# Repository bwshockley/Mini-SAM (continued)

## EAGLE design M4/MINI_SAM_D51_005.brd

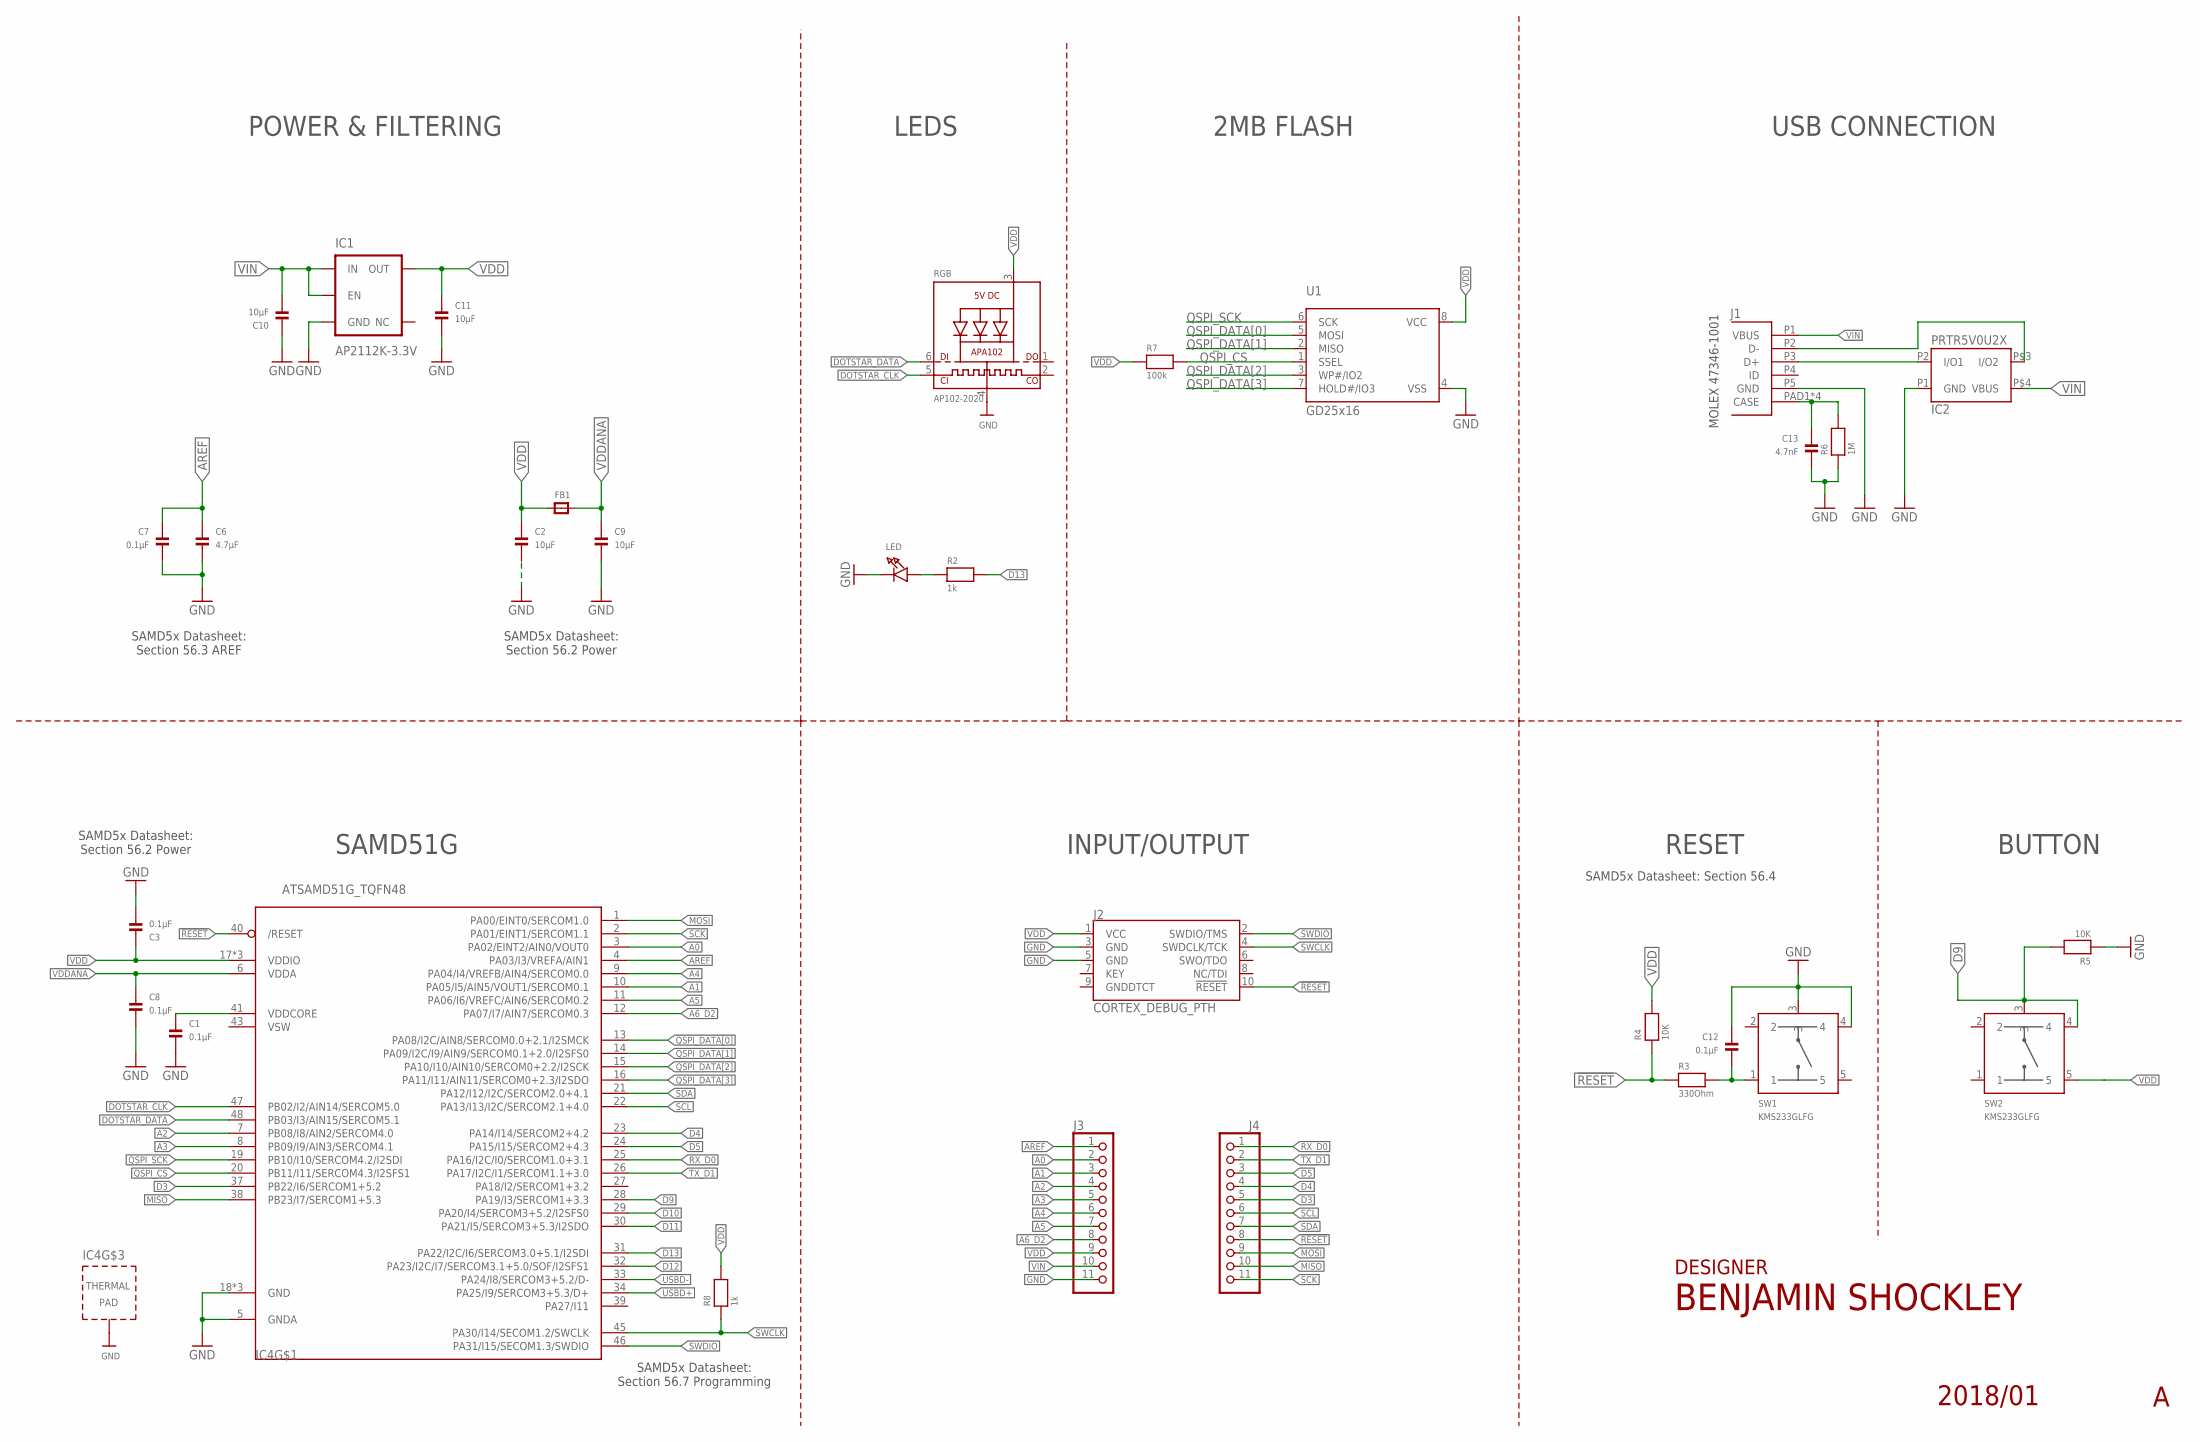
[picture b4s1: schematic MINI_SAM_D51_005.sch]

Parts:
C1, C3, C7, C8, C12: 0.1µF; _0603MP
C2, C9, C10, C11: 10µF; _0603MP
C6: 4.7µF; _0603MP
C13: 4.7nF; _0603MP
FB1: FERRITE_0603MP; _0603MP
IC1: AP2112K-3.3V; SOT23-5
IC2: PRTR5V0U2X; SOT143B_REFLOW
IC4: ATSAMD51G_TQFN48; TQFN48_7MM
J1: MOLEX_47346-100147346; MOLEX_47346-1001
J2: CORTEX_DEBUG_PTH; 2X5-PTH-1.27MM
J3, J4: PINHD-1X111X11_SMT; 1X11_SMT
LED: LED0603_NOOUTLINE; CHIPLED_0603_NOOUTLINE
R2, R8: 1k; _0603MP
R3: 330Ohm; _0603MP
R4, R5: 10K; _0603MP
R6: 1M; _0603MP
R7: 100k; _0603MP
RGB: AP102-2020; APA102_2020
SW1, SW2: KMS233GLFG; KMS_SWITCH
U1: GD25x16; USON8

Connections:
!RESET: IC4.40 (/RESET), J2.10 (!RESET), J4.8, R3.1, R4.1
A0: IC4.3 (PA02/EINT2/AIN0/VOUT0), J3.2
A1: IC4.10 (PA05/I5/AIN5/VOUT1/SERCOM0.1), J3.3
A2: IC4.7 (PB08/I8/AIN2/SERCOM4.0), J3.4
A3: IC4.8 (PB09/I9/AIN3/SERCOM4.1), J3.5
A4: IC4.9 (PA04/I4/VREFB/AIN4/SERCOM0.0), J3.6
A5: IC4.11 (PA06/I6/VREFC/AIN6/SERCOM0.2), J3.7
A6_D2: IC4.12 (PA07/I7/AIN7/SERCOM0.3), J3.8
AREF: C6.1, C7.1, IC4.4 (PA03/I3/VREFA/AIN1), J3.1
D3: IC4.37 (PB22/I6/SERCOM1+5.2), J4.5
D4: IC4.23 (PA14/I14/SERCOM2+4.2), J4.4
D5: IC4.24 (PA15/I15/SERCOM2+4.3), J4.3
D9: IC4.28 (PA19/I3/SERCOM1+3.3), R5.2, SW2.3, SW2.4
D10: IC4.29 (PA20/I4/SERCOM3+5.2/I2SFS0)
D11: IC4.30 (PA21/I5/SERCOM3+5.3/I2SDO)
D12: IC4.32 (PA23/I2C/I7/SERCOM3.1+5.0/SOF/I2SFS1)
D13: IC4.31 (PA22/I2C/I6/SERCOM3.0+5.1/I2SDI), R2.2
DOTSTAR_CLK: IC4.47 (PB02/I2/AIN14/SERCOM5.0), RGB.5 (CKI)
DOTSTAR_DATA: IC4.48 (PB03/I3/AIN15/SERCOM5.1), RGB.6 (DI)
GND: C1.2, C2.2, C3.2, C6.2, C7.2, C8.2, C9.2, C10.1, C11.2, C12.1, C13.2, IC1.2 (GND), IC2.P1 (GND), IC4.5 (GNDA), IC4.18 (GND), IC4.35 (GND), IC4.42 (GND), IC4.THERMAL (TP), J1.P5 (GND), J2.3 (GND), J2.5 (GND), J3.11, LED.C, R5.1, R6.1, RGB.4 (GND), SW1.3, SW1.4, U1.4 (VSS)
MISO: IC4.38 (PB23/I7/SERCOM1+5.3), J4.10
MOSI: IC4.1 (PA00/EINT0/SERCOM1.0), J4.9
unnamed: C13.1, J1.PAD1 (CASE), J1.PAD2 (CASE), J1.PAD3 (CASE), J1.PAD4 (CASE), R6.2
unnamed: LED.A, R2.1
unnamed: C12.2, R3.2, SW1.1
unnamed: C1.1, IC4.41 (VDDCORE)
QSPI_CS: IC4.20 (PB11/I11/SERCOM4.3/I2SFS1), R7.2, U1.1 (SSEL)
QSPI_DATA[0]: IC4.13 (PA08/I2C/AIN8/SERCOM0.0+2.1/I2SMCK), U1.5 (MOSI)
QSPI_DATA[1]: IC4.14 (PA09/I2C/I9/AIN9/SERCOM0.1+2.0/I2SFS0), U1.2 (MISO)
QSPI_DATA[2]: IC4.15 (PA10/I10/AIN10/SERCOM0+2.2/I2SCK), U1.3 (WP#/IO2)
QSPI_DATA[3]: IC4.16 (PA11/I11/AIN11/SERCOM0+2.3/I2SDO), U1.7 (HOLD#/IO3)
QSPI_SCK: IC4.19 (PB10/I10/SERCOM4.2/I2SDI), U1.6 (SCK)
RX_D0: IC4.25 (PA16/I2C/I0/SERCOM1.0+3.1), J4.1
SCK: IC4.2 (PA01/EINT1/SERCOM1.1), J4.11
SCL: IC4.22 (PA13/I13/I2C/SERCOM2.1+4.0), J4.6
SDA: IC4.21 (PA12/I12/I2C/SERCOM2.0+4.1), J4.7
SWCLK: IC4.45 (PA30/I14/SECOM1.2/SWCLK), J2.4 (SWDCLK/TCK), R8.1
SWDIO: IC4.46 (PA31/I15/SECOM1.3/SWDIO), J2.2 (SWDIO/TMS)
TX_D1: IC4.26 (PA17/I2C/I1/SERCOM1.1+3.0), J4.2
USBD+: IC2.P2 (I/O1), IC4.34 (PA25/I9/SERCOM3+5.3/D+), J1.P3 (D+)
USBD-: IC2.P$3 (I/O2), IC4.33 (PA24/I8/SERCOM3+5.2/D-), J1.P2 (D-)
VDD: C2.1, C3.1, C11.1, FB1.1, IC1.5 (OUT), IC4.17 (VDDIO), IC4.36 (VDDIO), IC4.44 (VDDIO), J2.1 (VCC), J3.9, R4.2, R7.1, R8.2, RGB.3 (VDD), SW2.5, U1.8 (VCC)
VDDANA: C8.1, C9.1, FB1.2, IC4.6 (VDDA)
VIN: C10.2, IC1.1 (IN), IC1.3 (EN), IC2.P$4 (VBUS), J1.P1 (VBUS), J3.10
VSW: IC4.43 (VSW)

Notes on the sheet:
INPUT/OUTPUT
RESET
POWER & FILTERING
SAMD51G
LEDS
USB CONNECTION
MOLEX 47346-1001
BUTTON
DESIGNER
SAMD5x Datasheet: Section 56.4
2MB FLASH
SAMD5x Datasheet: Section 56.3 AREF
SAMD5x Datasheet: Section 56.2 Power
SAMD5x Datasheet: Section 56.7 Programming

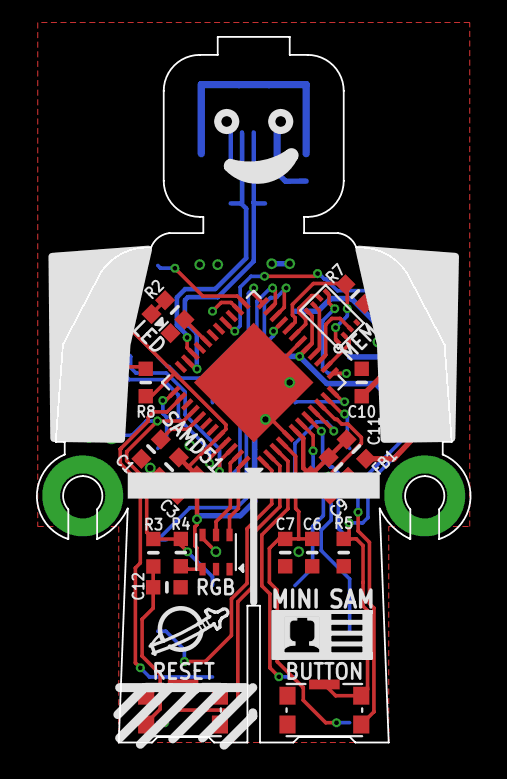
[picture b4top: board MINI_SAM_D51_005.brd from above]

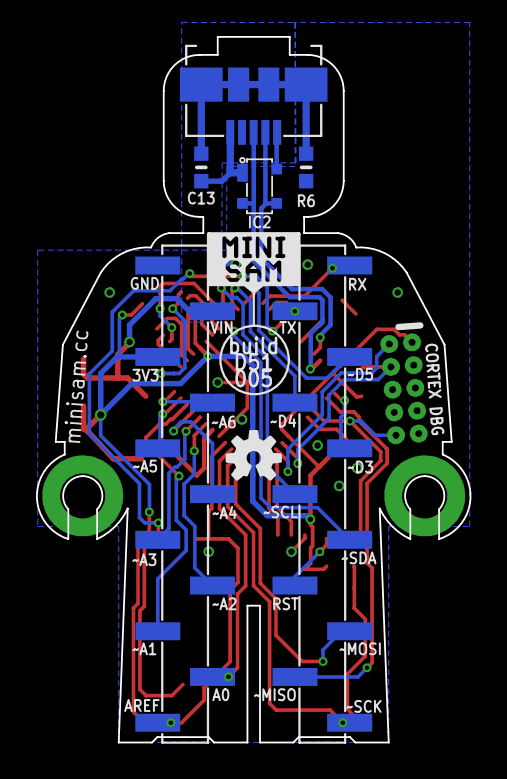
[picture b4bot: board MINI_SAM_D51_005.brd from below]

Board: 2 copper layers, 24.1 x 39.2 mm, 32 parts (7 on the bottom side), 41 nets.

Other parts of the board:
U$3: OSHW-LOGO-S

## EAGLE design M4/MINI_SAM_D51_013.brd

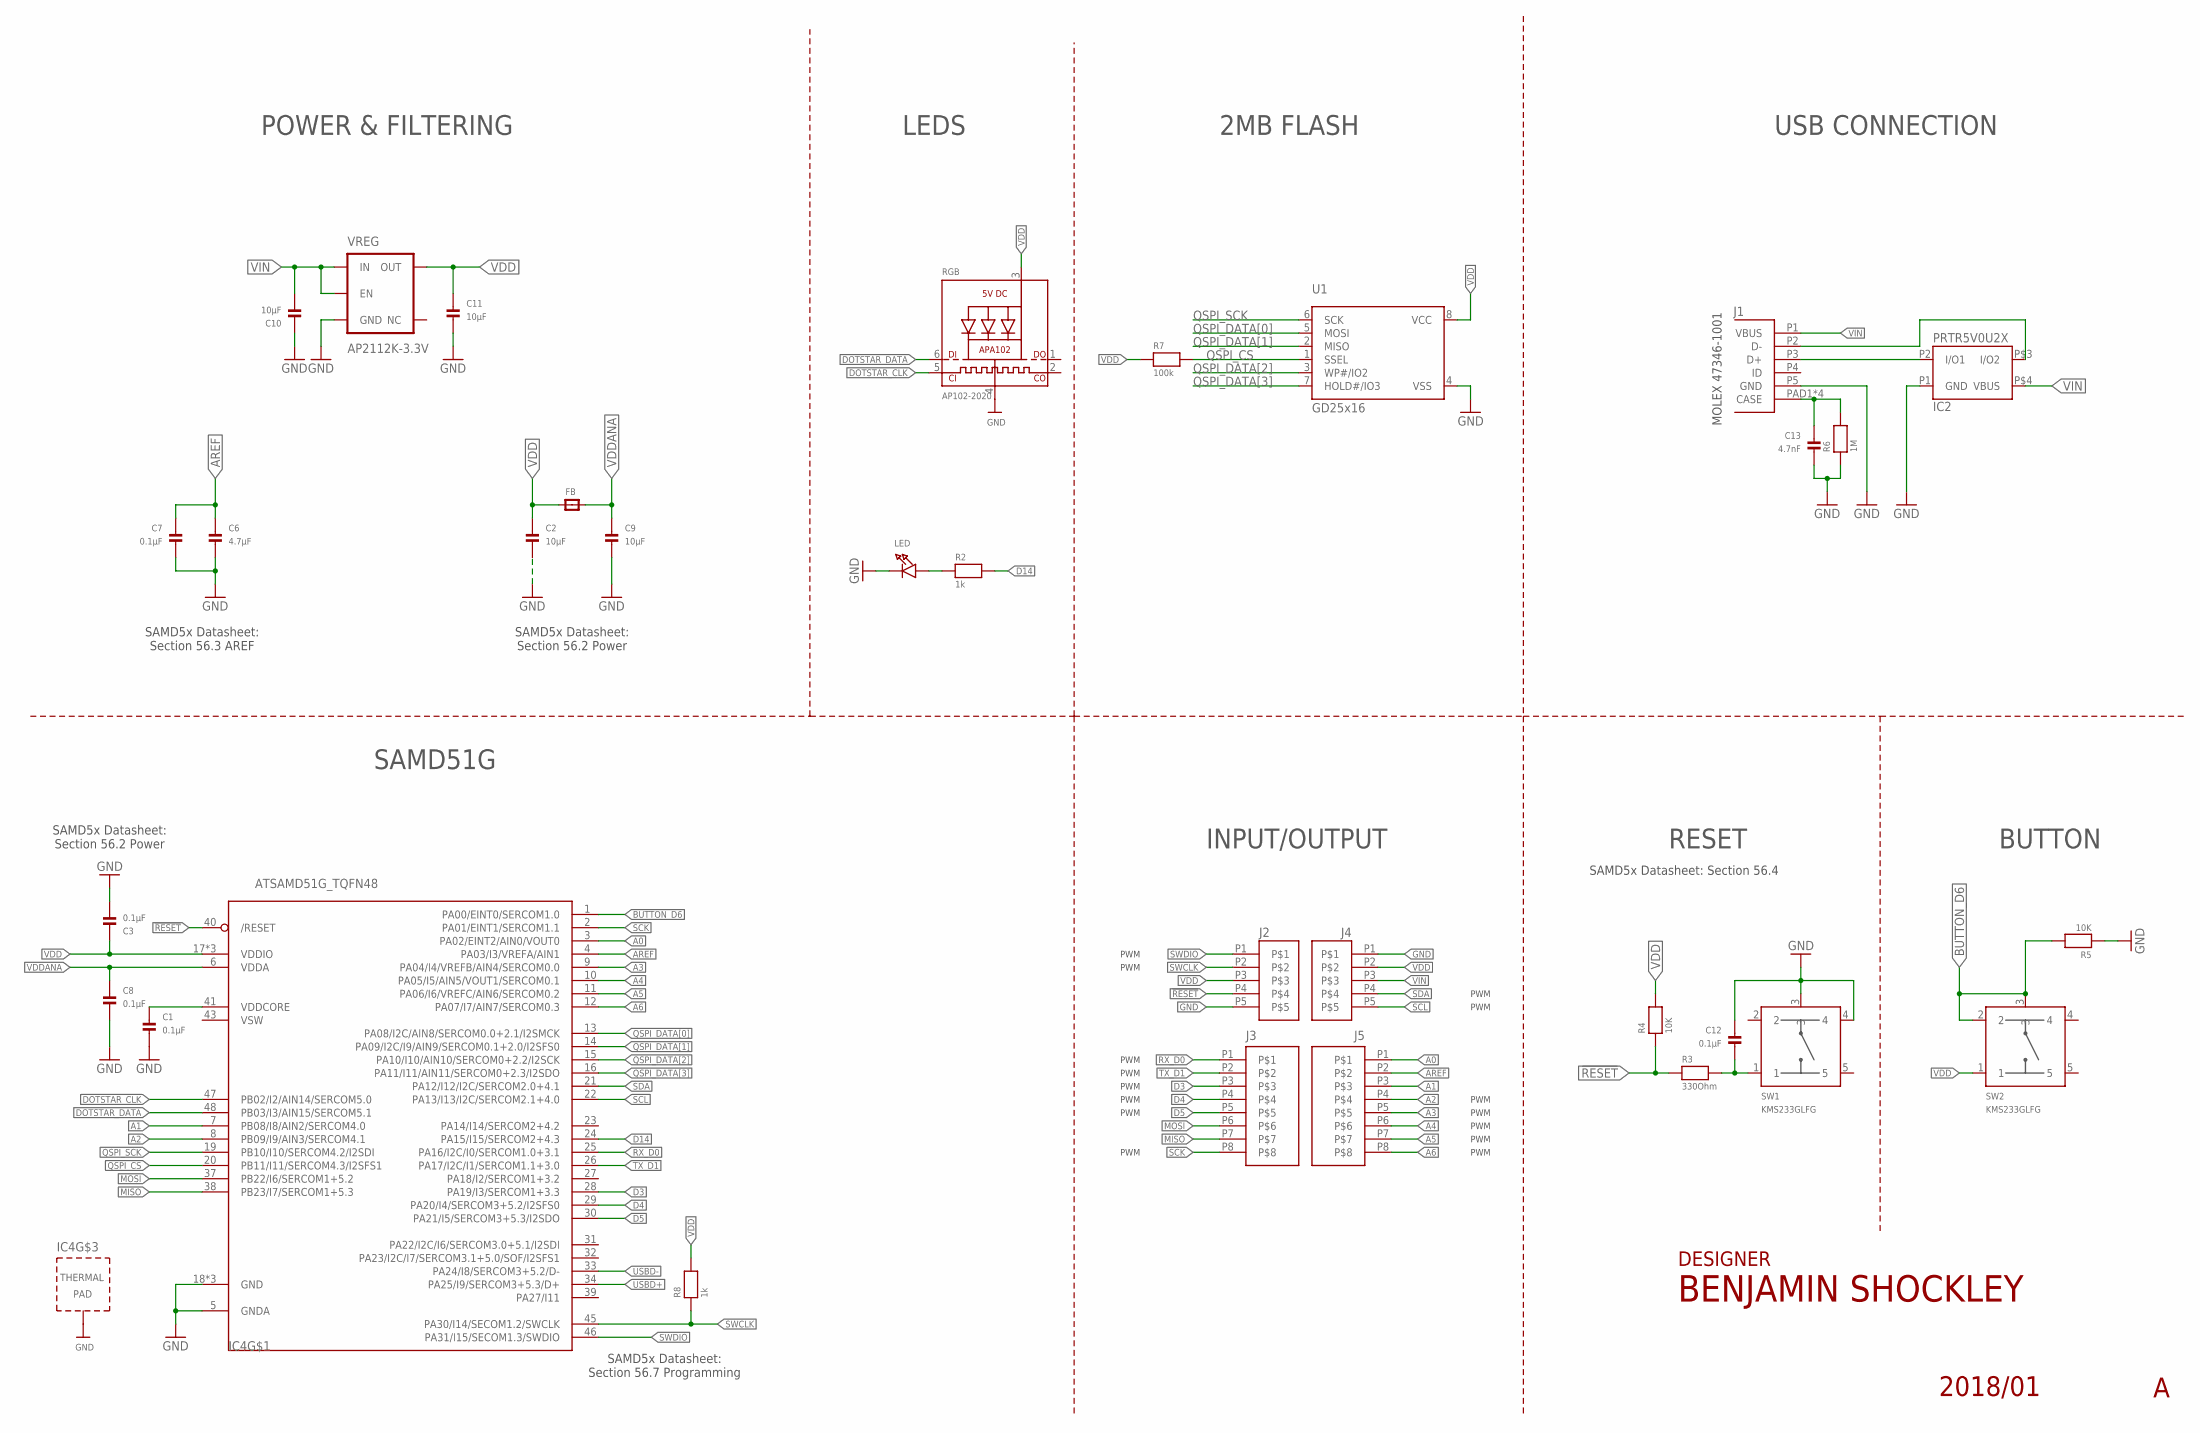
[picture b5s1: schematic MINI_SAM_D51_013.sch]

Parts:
C1, C3, C7, C8, C12: 0.1µF; _0603MP
C2, C9, C10, C11: 10µF; _0603MP
C6: 4.7µF; _0603MP
C13: 4.7nF; _0603MP
FB: FERRITE_0603MP; _0603MP
IC2: PRTR5V0U2X; SOT143B_REFLOW
IC4: ATSAMD51G_TQFN48; TQFN48_7MM
J1: MOLEX_47346-100147346; MOLEX_47346-1001
J2, J4: 1X5_HEADER_1.27MMCAST; 1X5_HEADER_1.27MM_CASTELLATED
J3, J5: 1X8_HEADER_1.27MMCAST; 1X8_HEADER_1.27MM_CASTELLATED
LED: LED0805_NOOUTLINE; CHIPLED_0805_NOOUTLINE
R2, R8: 1k; _0603MP
R3: 330Ohm; _0603MP
R4, R5: 10K; _0603MP
R6: 1M; _0603MP
R7: 100k; _0603MP
RGB: AP102-2020; APA102_2020
SW1, SW2: KMS233GLFG; KMS_SWITCH
U1: GD25x16; USON8
VREG: AP2112K-3.3V; SOT23-5

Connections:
!RESET: IC4.40 (/RESET), J2.P4, R3.1, R4.1
A0: IC4.3 (PA02/EINT2/AIN0/VOUT0), J5.P1
A1: IC4.7 (PB08/I8/AIN2/SERCOM4.0), J5.P3
A2: IC4.8 (PB09/I9/AIN3/SERCOM4.1), J5.P4
A3: IC4.9 (PA04/I4/VREFB/AIN4/SERCOM0.0), J5.P5
A4: IC4.10 (PA05/I5/AIN5/VOUT1/SERCOM0.1), J5.P6
A5: IC4.11 (PA06/I6/VREFC/AIN6/SERCOM0.2), J5.P7
A6: IC4.12 (PA07/I7/AIN7/SERCOM0.3), J5.P8
AREF: C6.1, C7.1, IC4.4 (PA03/I3/VREFA/AIN1), J5.P2
BUTTON_D6: IC4.1 (PA00/EINT0/SERCOM1.0), R5.2, SW2.2, SW2.3
D3: IC4.28 (PA19/I3/SERCOM1+3.3), J3.P3
D4: IC4.29 (PA20/I4/SERCOM3+5.2/I2SFS0), J3.P4
D5: IC4.30 (PA21/I5/SERCOM3+5.3/I2SDO), J3.P5
D14: IC4.24 (PA15/I15/SERCOM2+4.3), R2.2
DOTSTAR_CLK: IC4.47 (PB02/I2/AIN14/SERCOM5.0), RGB.5 (CKI)
DOTSTAR_DATA: IC4.48 (PB03/I3/AIN15/SERCOM5.1), RGB.6 (DI)
GND: C1.2, C2.2, C3.2, C6.2, C7.2, C8.2, C9.2, C10.1, C11.2, C12.1, C13.2, IC2.P1 (GND), IC4.5 (GNDA), IC4.18 (GND), IC4.35 (GND), IC4.42 (GND), IC4.THERMAL (TP), J1.P5 (GND), J2.P5, J4.P1, LED.C, R5.1, R6.1, RGB.4 (GND), SW1.3, SW1.4, U1.4 (VSS), VREG.2 (GND)
MISO: IC4.38 (PB23/I7/SERCOM1+5.3), J3.P7
MOSI: IC4.37 (PB22/I6/SERCOM1+5.2), J3.P6
unnamed: C13.1, J1.PAD1 (CASE), J1.PAD2 (CASE), J1.PAD3 (CASE), J1.PAD4 (CASE), R6.2
unnamed: LED.A, R2.1
unnamed: C12.2, R3.2, SW1.1
unnamed: C1.1, IC4.41 (VDDCORE)
QSPI_CS: IC4.20 (PB11/I11/SERCOM4.3/I2SFS1), R7.2, U1.1 (SSEL)
QSPI_DATA[0]: IC4.13 (PA08/I2C/AIN8/SERCOM0.0+2.1/I2SMCK), U1.5 (MOSI)
QSPI_DATA[1]: IC4.14 (PA09/I2C/I9/AIN9/SERCOM0.1+2.0/I2SFS0), U1.2 (MISO)
QSPI_DATA[2]: IC4.15 (PA10/I10/AIN10/SERCOM0+2.2/I2SCK), U1.3 (WP#/IO2)
QSPI_DATA[3]: IC4.16 (PA11/I11/AIN11/SERCOM0+2.3/I2SDO), U1.7 (HOLD#/IO3)
QSPI_SCK: IC4.19 (PB10/I10/SERCOM4.2/I2SDI), U1.6 (SCK)
RX_D0: IC4.25 (PA16/I2C/I0/SERCOM1.0+3.1), J3.P1
SCK: IC4.2 (PA01/EINT1/SERCOM1.1), J3.P8
SCL: IC4.22 (PA13/I13/I2C/SERCOM2.1+4.0), J4.P5
SDA: IC4.21 (PA12/I12/I2C/SERCOM2.0+4.1), J4.P4
SWCLK: IC4.45 (PA30/I14/SECOM1.2/SWCLK), J2.P2, R8.1
SWDIO: IC4.46 (PA31/I15/SECOM1.3/SWDIO), J2.P1
TX_D1: IC4.26 (PA17/I2C/I1/SERCOM1.1+3.0), J3.P2
USBD+: IC2.P2 (I/O1), IC4.34 (PA25/I9/SERCOM3+5.3/D+), J1.P3 (D+)
USBD-: IC2.P$3 (I/O2), IC4.33 (PA24/I8/SERCOM3+5.2/D-), J1.P2 (D-)
VDD: C2.1, C3.1, C11.1, FB.1, IC4.17 (VDDIO), IC4.36 (VDDIO), IC4.44 (VDDIO), J2.P3, J4.P2, R4.2, R7.1, R8.2, RGB.3 (VDD), SW2.1, U1.8 (VCC), VREG.5 (OUT)
VDDANA: C8.1, C9.1, FB.2, IC4.6 (VDDA)
VIN: C10.2, IC2.P$4 (VBUS), J1.P1 (VBUS), J4.P3, VREG.1 (IN), VREG.3 (EN)
VSW: IC4.43 (VSW)

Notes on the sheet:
INPUT/OUTPUT
RESET
POWER & FILTERING
SAMD51G
LEDS
USB CONNECTION
MOLEX 47346-1001
BUTTON
DESIGNER
SAMD5x Datasheet: Section 56.4
2MB FLASH
SAMD5x Datasheet: Section 56.3 AREF
SAMD5x Datasheet: Section 56.2 Power
SAMD5x Datasheet: Section 56.7 Programming
PWM

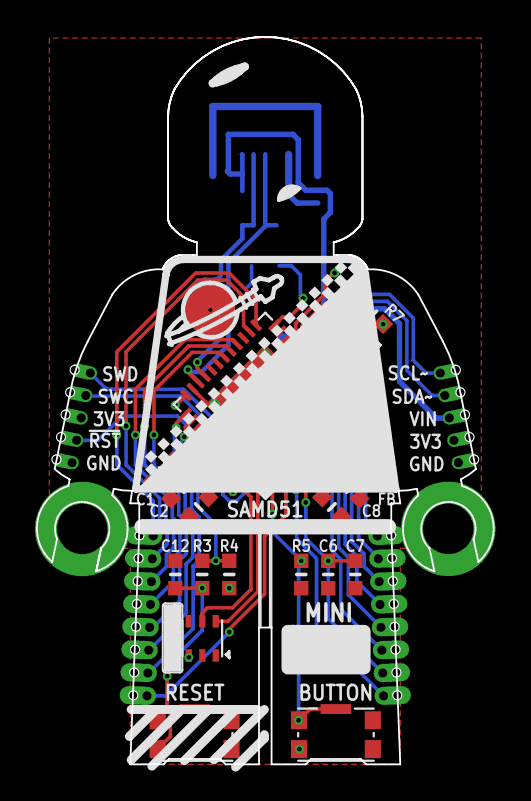
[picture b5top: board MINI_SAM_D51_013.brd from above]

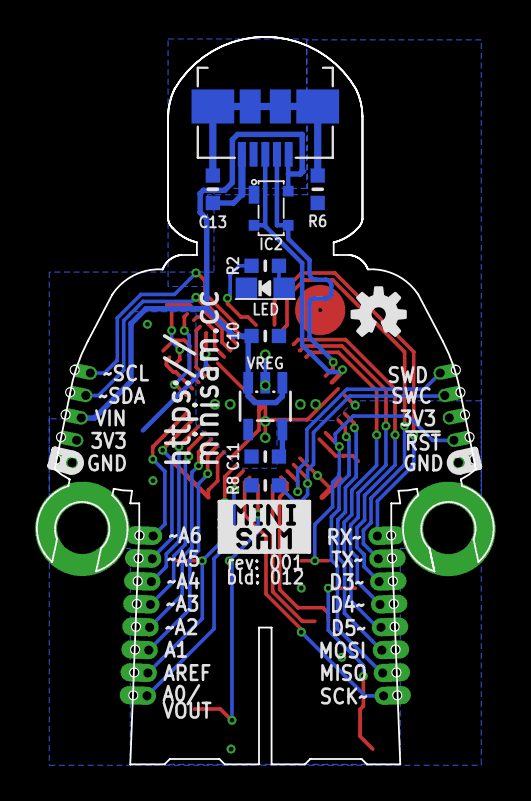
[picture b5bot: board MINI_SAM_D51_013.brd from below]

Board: 2 copper layers, 25.4 x 40.4 mm, 33 parts (11 on the bottom side), 41 nets.

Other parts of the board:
U$3: OSHW-LOGO-S

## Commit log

2018-07-25 Initial Commit
    Adding inital files to the repository.
2018-07-26 Updated to 006
    Mostly cosmetic updates, some associated component re-arranging.
2018-07-26 More minor cosmetic changes
    Minor updates to board design and cosmetic changes.
2018-07-31 Created Version 007
    Changed USB routes to match each other in length. Increased size of space logo - rearranged a couple vias in the process.
2018-07-31 Removed Face tCream
    Removed the eyes and mouth tCream items that were inadvertantly added.
2018-07-31 Created SAMD51-007 BOM
    Text output from EAGLE - Needs cleaning but a good start.
2018-07-31 Added v 007 Schematic
2018-07-31 Updated -007 BOM
    Cleaned up and added some clarity.
2018-07-31 Added
2018-08-08 Added Rev 008
2018-08-08 Slight Update to Rev 007
2018-08-10 Adjust VREG
    Tried a new layout with VREG aligned to torso.
2018-08-14 Name Changes
2018-08-14 Minor Mods
    Modified layout slightly. Will require a new sold paste template.
2018-08-20 Added details for 2MB Flash
    I can't find too many USON-8 2x3mm flash devices, so I'm open to adding more options to the list.
2018-08-20 Updated 2MB Flash Description
    Added updated description.
2018-10-02 Adding revisions
2018-10-02 UF2 Bootloader Link
    Added link to repository where the Mini Sam M4 UF2 bootloader can be built.
2018-10-02 Update and rename SAMD51-007 to SAMD51-007.md
    BOM error message
2018-10-02 Updated VDDCORE Cap
    Updated VDDCORE cap to 4.7uF.
2018-10-03 BOM Cleanup
    Cleanup of Rev 016 BOM.
2018-10-03 QSPI Flash description update.
2018-11-06 Set theme jekyll-theme-minimal
2018-12-07 Updated Board Designs
    Added new design revisions
2018-12-07 Create Mini_SAM_D51_r017
    BOM for R017 version boards. These boards use a PLCC-2 reverse gullwing led on the back.
2018-12-07 Release 017 Only
    Set to Release 017 only.
2018-12-07 File Relocations
    Moving files to combine M0 and M4 Mini SAM variants.
2018-12-07 Create LICENSE
2018-12-07 Adding new Mini SAM M0
2019-02-02 Added bootloader and firmware
2019-05-15 Added Board
2019-09-11 Update and rename Mini_SAM_D51_r017 to Mini_SAM_M4
2019-09-11 Added Rev 025
2019-09-23 Update README.md
    typo
2020-01-02 Add AfterDark Source Files
    Added the PCB source files for the Afterdark version. This removes ground fills and adds a hole for backlit LED. Use this file with OSHPARK Afterdark service.
